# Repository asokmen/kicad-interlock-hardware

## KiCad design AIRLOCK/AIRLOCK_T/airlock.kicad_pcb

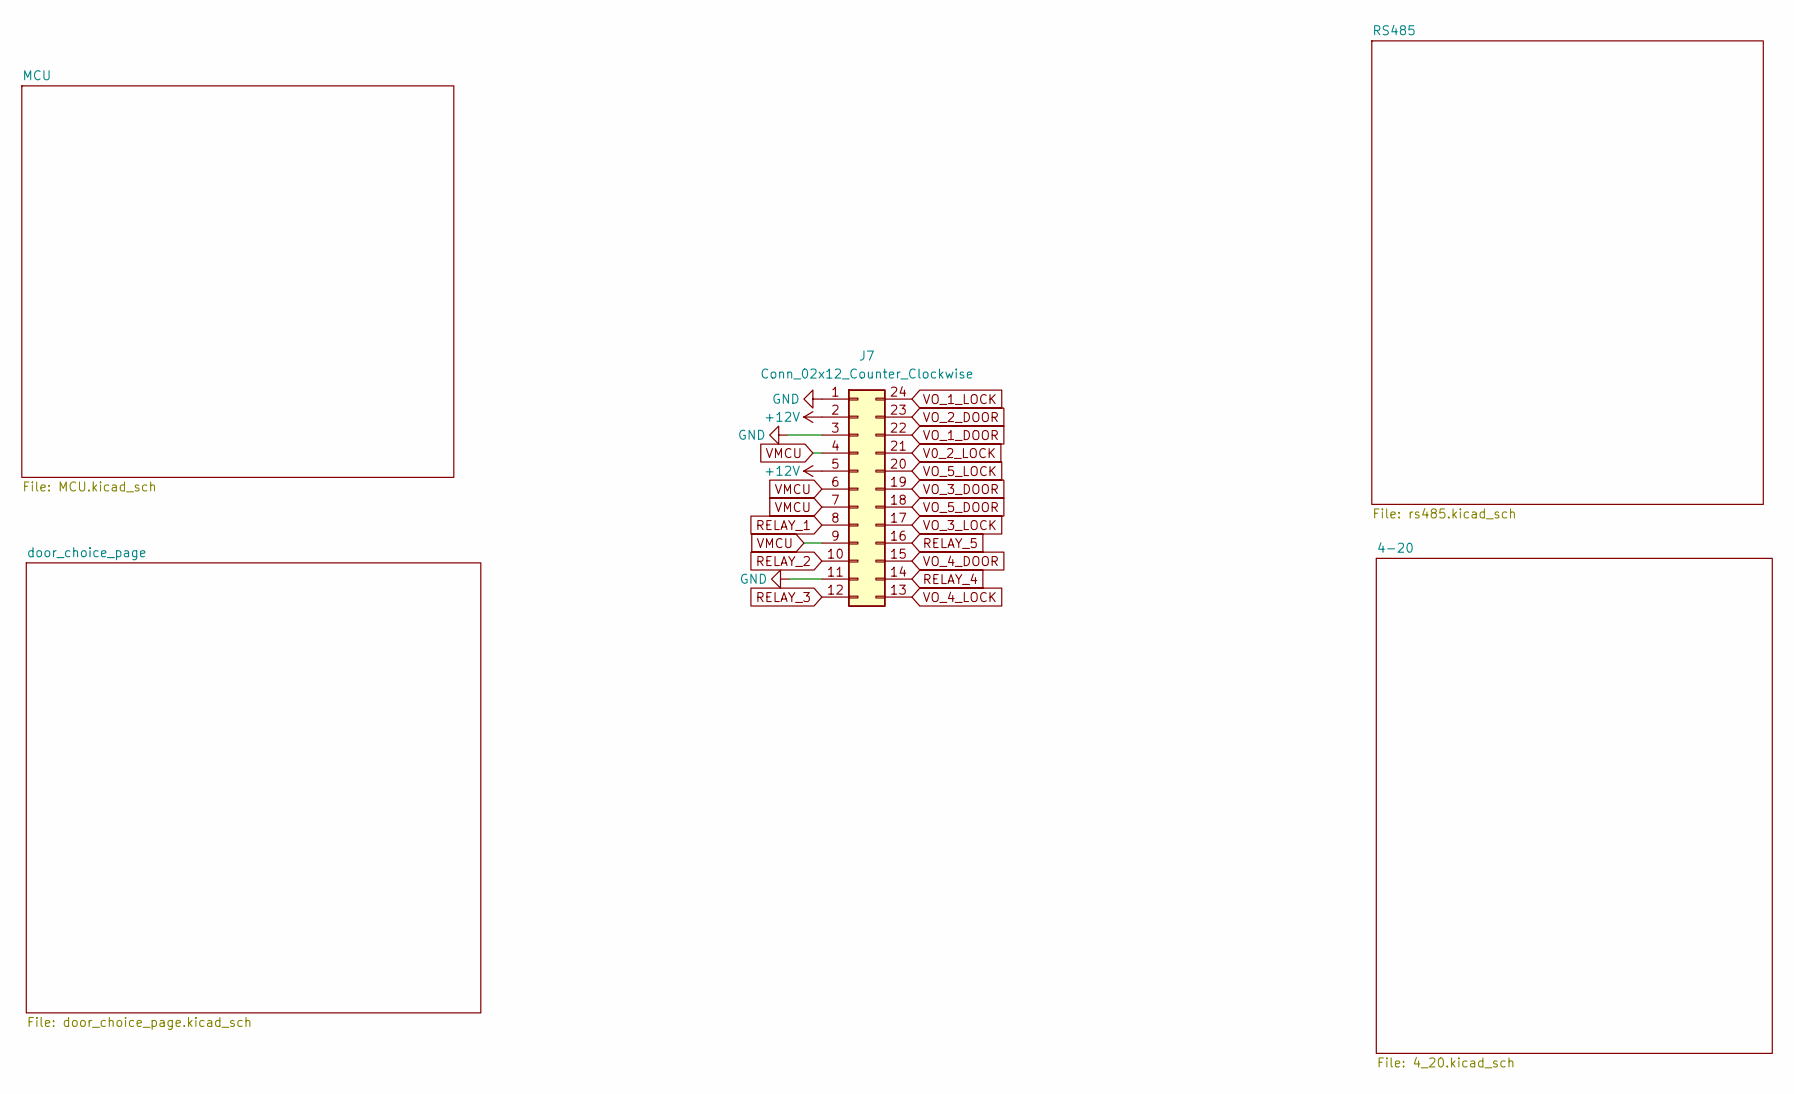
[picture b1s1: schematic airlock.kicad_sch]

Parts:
J7: Conn_02x12_Counter_Clockwise; PinHeader_2x12_P2.54mm_Vertical

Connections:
12v: J7.2, J7.5; also elsewhere on the board
GND: J7.1, J7.3, J7.11; also elsewhere on the board
RELAY_1: J7.8; also elsewhere on the board
RELAY_2: J7.10; also elsewhere on the board
RELAY_3: J7.12; also elsewhere on the board
RELAY_4: J7.14; also elsewhere on the board
RELAY_5: J7.16; also elsewhere on the board
V0_2_LOCK: J7.21; also elsewhere on the board
VMCU: J7.4, J7.6, J7.7, J7.9; also elsewhere on the board
VO_1_DOOR: J7.22; also elsewhere on the board
VO_1_LOCK: J7.24; also elsewhere on the board
VO_2_DOOR: J7.23; also elsewhere on the board
VO_3_DOOR: J7.19; also elsewhere on the board
VO_3_LOCK: J7.17; also elsewhere on the board
VO_4_DOOR: J7.15; also elsewhere on the board
VO_4_LOCK: J7.13; also elsewhere on the board
VO_5_DOOR: J7.18; also elsewhere on the board
VO_5_LOCK: J7.20; also elsewhere on the board

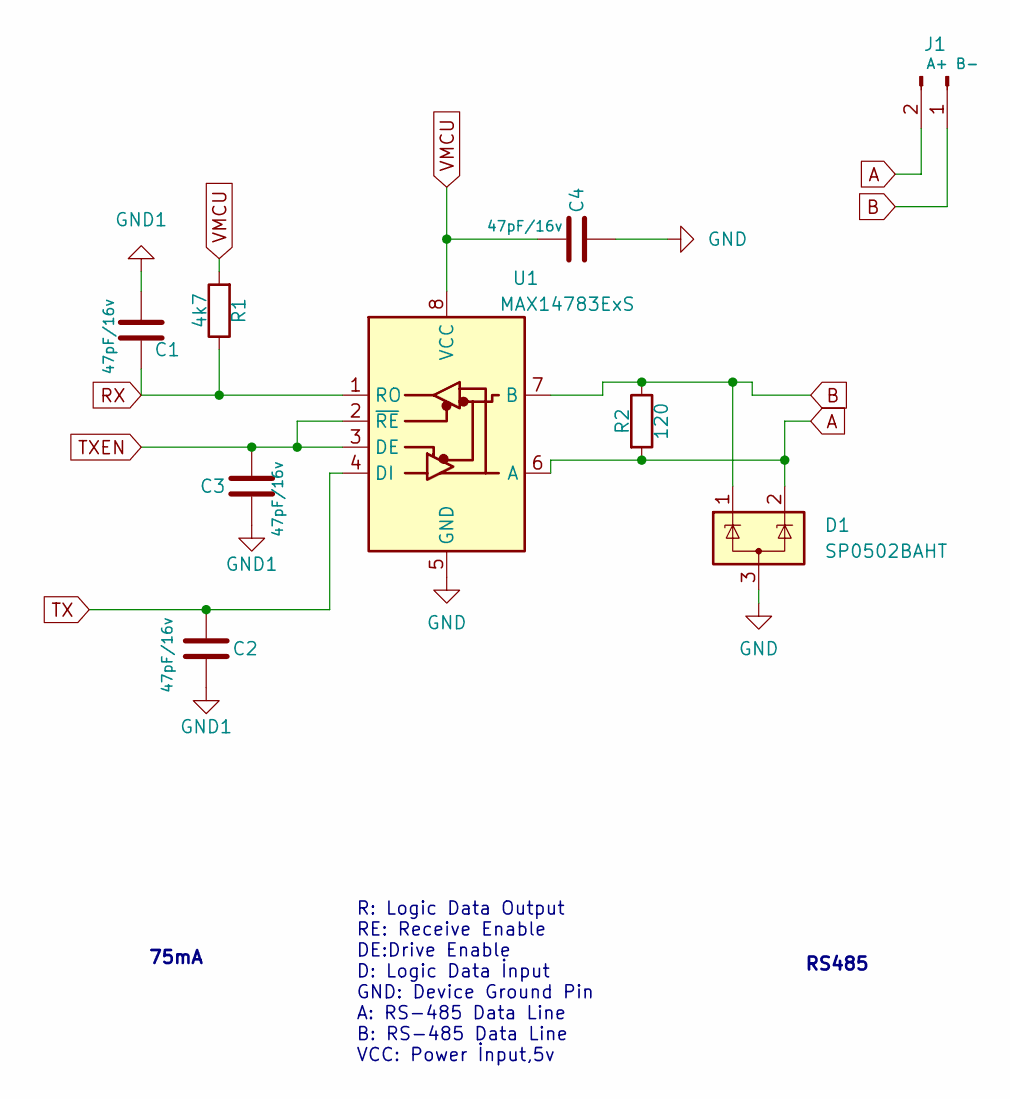
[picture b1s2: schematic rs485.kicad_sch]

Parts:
C1, C2, C3, C4: 47pF/16v; C_0805_2012Metric
D1: SP0502BAHT; SOT-23
J1: A+ B-; terminalblock_vertical_10.20mmx11.94mm
R1: 4k7; as_0805_res
R2: 120; as_0805_res
U1: MAX14783ExS; SOIC-8_3.9x4.9mm_P1.27mm

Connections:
A: D1.2 (K), J1.2, R2.2, U1.6 (A)
B: D1.1 (K), J1.1, R2.1, U1.7 (B)
GND: C4.1, D1.3 (A), U1.5 (GND); also elsewhere on the board
GND1: C1.2, C2.1, C3.2
RX: C1.1, R1.1, U1.1 (RO); also elsewhere on the board
TX: C2.2, U1.4 (DI); also elsewhere on the board
TXEN: C3.1, U1.2 (~RE), U1.3 (DE); also elsewhere on the board
VMCU: C4.2, R1.2, U1.8 (VCC); also elsewhere on the board

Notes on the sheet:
RS485
75mA
R: Logic Data Output RE: Receive Enable DE:Drive Enable D: Logic Data İnput GND: Device Ground Pin A: RS-485 Data Line B: RS-485 Data Line VCC: Power İnput,5v

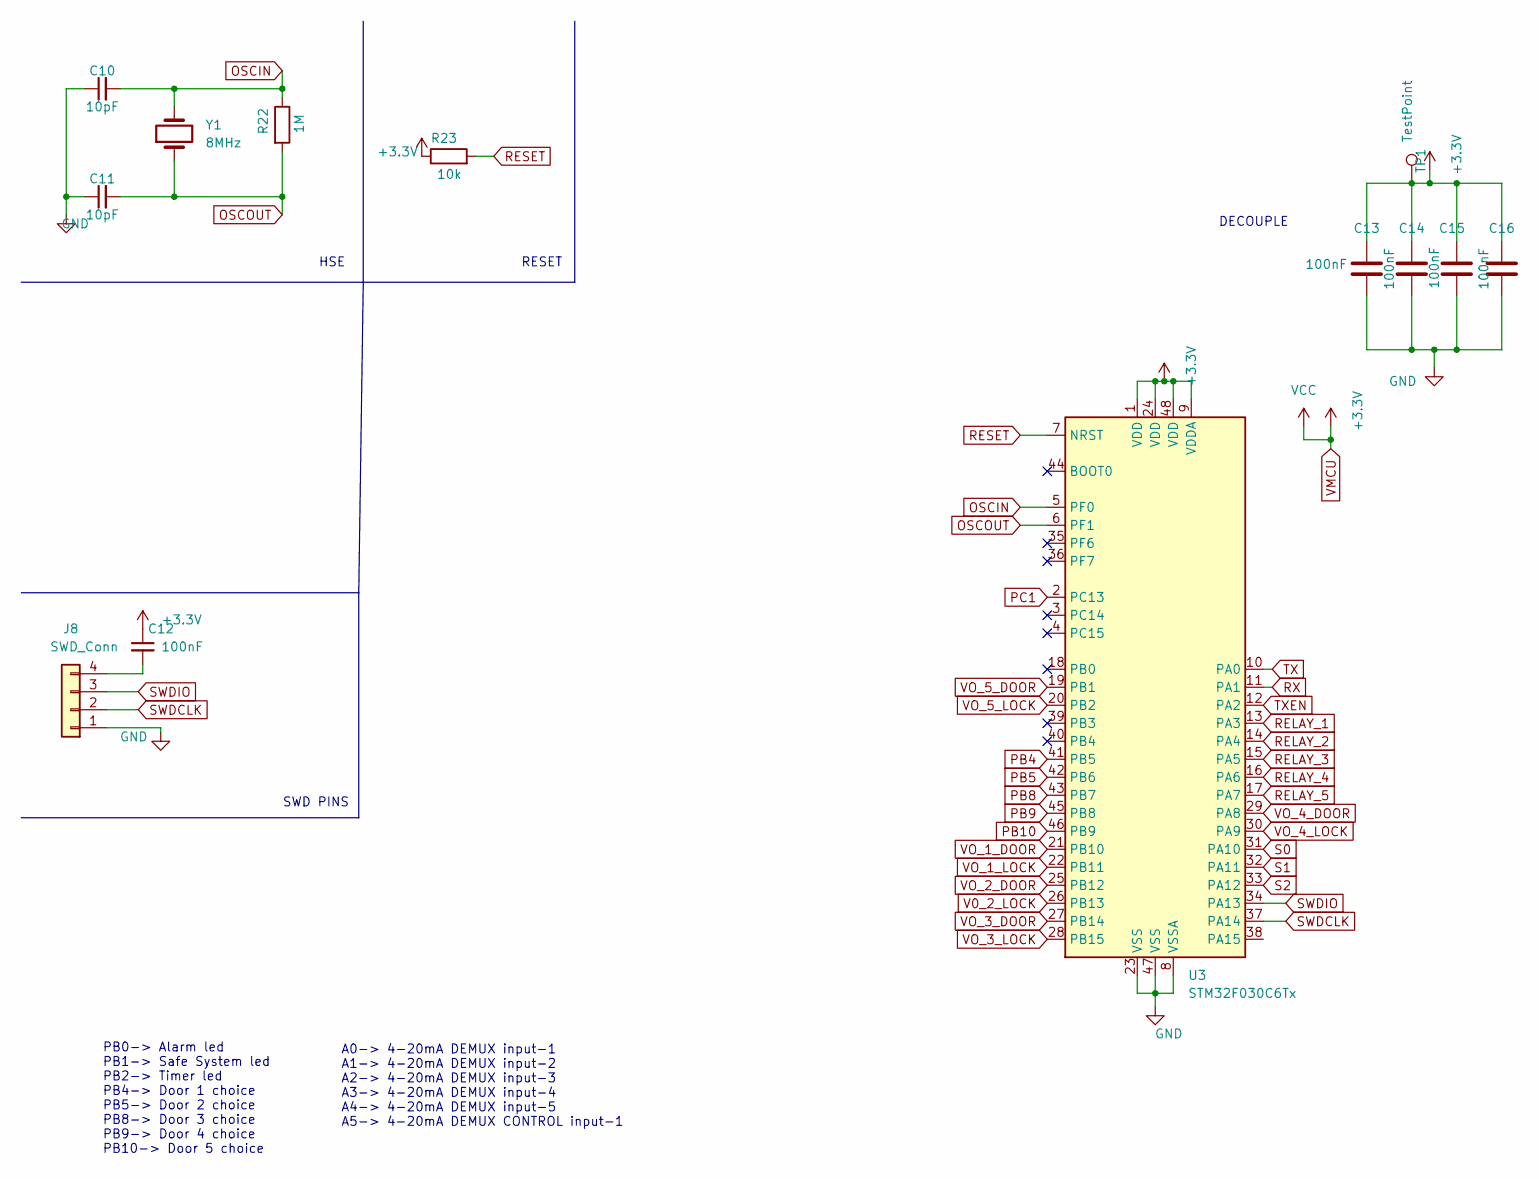
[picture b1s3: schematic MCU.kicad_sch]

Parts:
C10, C11: 10pF; C_0201_0603Metric
C12, C13, C14, C15, C16: 100nF; C_0603_1608Metric
J8: SWD_Conn; PinHeader_1x04_P2.54mm_Vertical
R22: 1M; as_0805_res
R23: 10k; as_0805_res
TP1: TestPoint; PinHeader_1x01_P1.00mm_Vertical
U3: STM32F030C6Tx; LQFP-48_7x7mm_P0.5mm
Y1: 8MHz; Crystal_HC49-4H_Vertical

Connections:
GND: C10.1, C11.1, C13.1, C14.1, C15.1, C16.1, J8.1, U3.8 (VSSA), U3.23 (VSS), U3.47 (VSS); also elsewhere on the board
unnamed: C12.2, J8.4
OSCIN: C10.2, R22.1, U3.5 (PF0), Y1.2
OSCOUT: C11.2, R22.2, U3.6 (PF1), Y1.1
PB4: U3.41 (PB5); also elsewhere on the board
PB5: U3.42 (PB6); also elsewhere on the board
PB8: U3.43 (PB7); also elsewhere on the board
PB9: U3.45 (PB8); also elsewhere on the board
PB10: U3.46 (PB9); also elsewhere on the board
PC1: U3.2 (PC13)
RELAY_1: U3.13 (PA3); also elsewhere on the board
RELAY_2: U3.14 (PA4); also elsewhere on the board
RELAY_3: U3.15 (PA5); also elsewhere on the board
RELAY_4: U3.16 (PA6); also elsewhere on the board
RELAY_5: U3.17 (PA7); also elsewhere on the board
RESET: R23.2, U3.7 (NRST)
RX: U3.11 (PA1); also elsewhere on the board
S0: U3.31 (PA10); also elsewhere on the board
S1: U3.32 (PA11); also elsewhere on the board
S2: U3.33 (PA12); also elsewhere on the board
SWDCLK: J8.2, U3.37 (PA14)
SWDIO: J8.3, U3.34 (PA13)
TX: U3.10 (PA0); also elsewhere on the board
TXEN: U3.12 (PA2); also elsewhere on the board
V0_2_LOCK: U3.26 (PB13); also elsewhere on the board
VMCU: C12.1, C13.2, C14.2, C15.2, C16.2, R23.1, TP1.1, U3.1 (VDD), U3.9 (VDDA), U3.24 (VDD), U3.48 (VDD); also elsewhere on the board
VO_1_DOOR: U3.21 (PB10); also elsewhere on the board
VO_1_LOCK: U3.22 (PB11); also elsewhere on the board
VO_2_DOOR: U3.25 (PB12); also elsewhere on the board
VO_3_DOOR: U3.27 (PB14); also elsewhere on the board
VO_3_LOCK: U3.28 (PB15); also elsewhere on the board
VO_4_DOOR: U3.29 (PA8); also elsewhere on the board
VO_4_LOCK: U3.30 (PA9); also elsewhere on the board
VO_5_DOOR: U3.19 (PB1); also elsewhere on the board
VO_5_LOCK: U3.20 (PB2); also elsewhere on the board

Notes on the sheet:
PB0-> Alarm led PB1-> Safe System led PB2-> Timer led PB4-> Door 1 choice PB5-> Door 2 choice PB8-> Door 3 choice PB9-> Door 4 choice PB10-> Door 5 choice
HSE
DECOUPLE
RESET
SWD PINS
A0-> 4-20mA DEMUX input-1 A1-> 4-20mA DEMUX input-2 A2-> 4-20mA DEMUX input-3 A3-> 4-20mA DEMUX input-4 A4-> 4-20mA DEMUX input-5 A5-> 4-20mA DEMUX CONTROL input-1

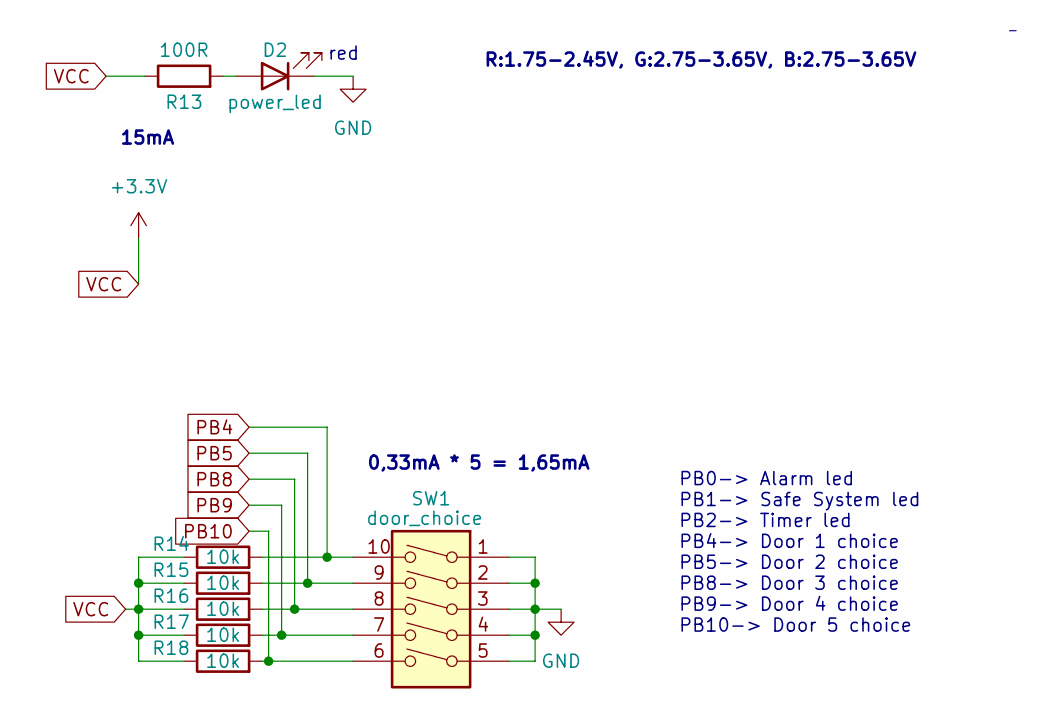
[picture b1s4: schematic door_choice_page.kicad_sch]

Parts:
D2: power_led; LED_0805_2012Metric
R13: 100R; as_0603_res
R14, R15, R16, R17, R18: 10k; as_0603_res
SW1: door_choice; SW_DIP_SPSTx05_Piano_10.8x14.26mm_W7.62mm_P2.54mm

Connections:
GND: D2.1 (K), SW1.1, SW1.2, SW1.3, SW1.4, SW1.5; also elsewhere on the board
unnamed: D2.2 (A), R13.2
PB4: R14.2, SW1.10; also elsewhere on the board
PB5: R15.2, SW1.9; also elsewhere on the board
PB8: R16.2, SW1.8; also elsewhere on the board
PB9: R17.2, SW1.7; also elsewhere on the board
PB10: R18.2, SW1.6; also elsewhere on the board
VMCU: R13.1, R14.1, R15.1, R16.1, R17.1, R18.1; also elsewhere on the board

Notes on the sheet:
R:1.75-2.45V, G:2.75-3.65V, B:2.75-3.65V
PB0-> Alarm led PB1-> Safe System led PB2-> Timer led PB4-> Door 1 choice PB5-> Door 2 choice PB8-> Door 3 choice PB9-> Door 4 choice PB10-> Door 5 choice
15mA
red
0,33mA * 5 = 1,65mA

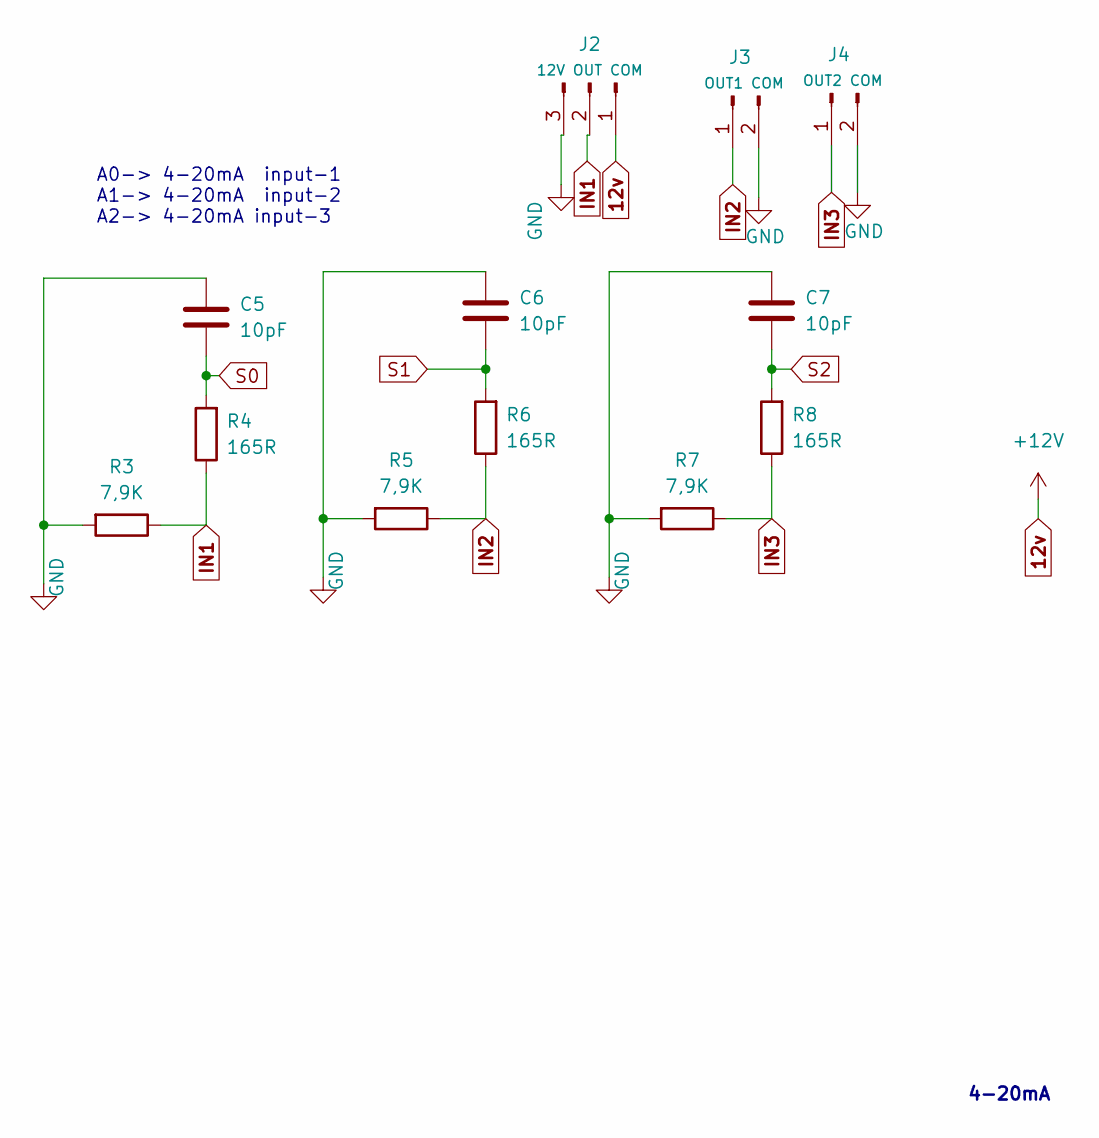
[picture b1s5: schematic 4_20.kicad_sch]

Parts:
C5, C6, C7: 10pF; C_0603_1608Metric
J2: 12V OUT COM; as_terminal_1x3
J3: OUT1 COM; terminalblock_vertical_10.20mmx11.94mm
J4: OUT2 COM; terminalblock_vertical_10.20mmx11.94mm
R3, R5, R7: 7,9K; as_0603_res
R4, R6, R8: 165R; as_0603_res

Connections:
12v: J2.1; also elsewhere on the board
GND: C5.2, C6.2, C7.2, J2.3, J3.2, J4.2, R3.2, R5.2, R7.2; also elsewhere on the board
IN1: J2.2, R3.1, R4.1
IN2: J3.1, R5.1, R6.1
IN3: J4.1, R7.1, R8.1
S0: C5.1, R4.2; also elsewhere on the board
S1: C6.1, R6.2; also elsewhere on the board
S2: C7.1, R8.2; also elsewhere on the board

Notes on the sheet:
A0-> 4-20mA input-1 A1-> 4-20mA input-2 A2-> 4-20mA input-3
4-20mA

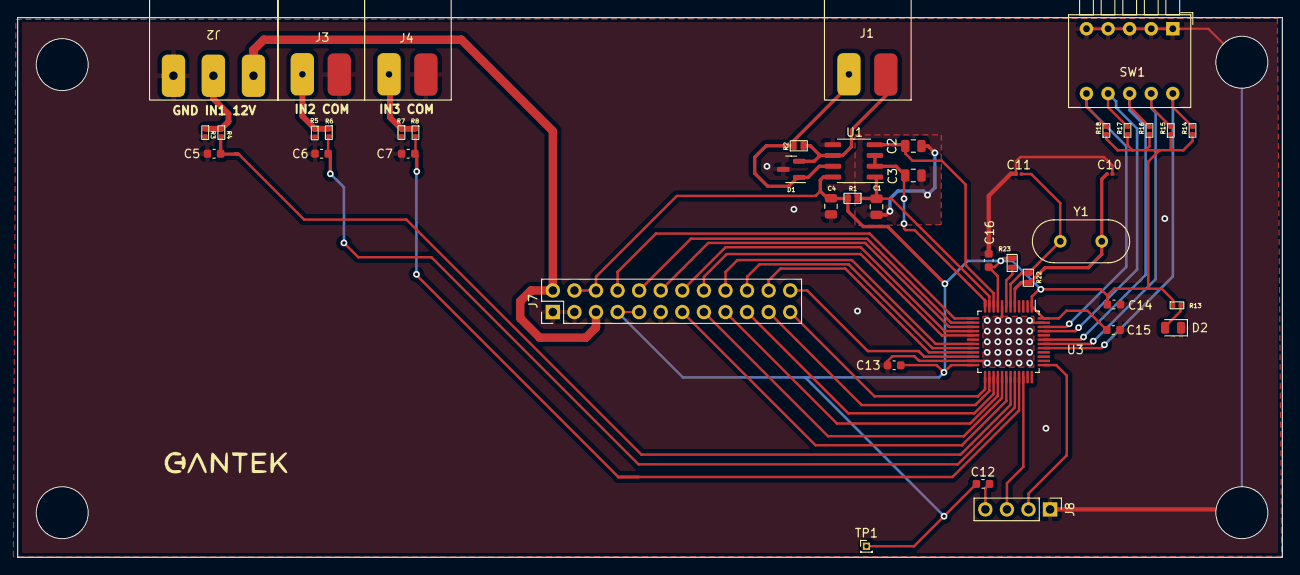
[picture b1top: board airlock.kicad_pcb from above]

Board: 2 copper layers, 148.9 x 63.5 mm, 43 parts (0 on the bottom side), 42 nets.
